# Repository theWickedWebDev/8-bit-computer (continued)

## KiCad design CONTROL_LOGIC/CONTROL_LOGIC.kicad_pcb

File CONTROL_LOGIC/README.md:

# Display Module

MORE DETAILS TO COME

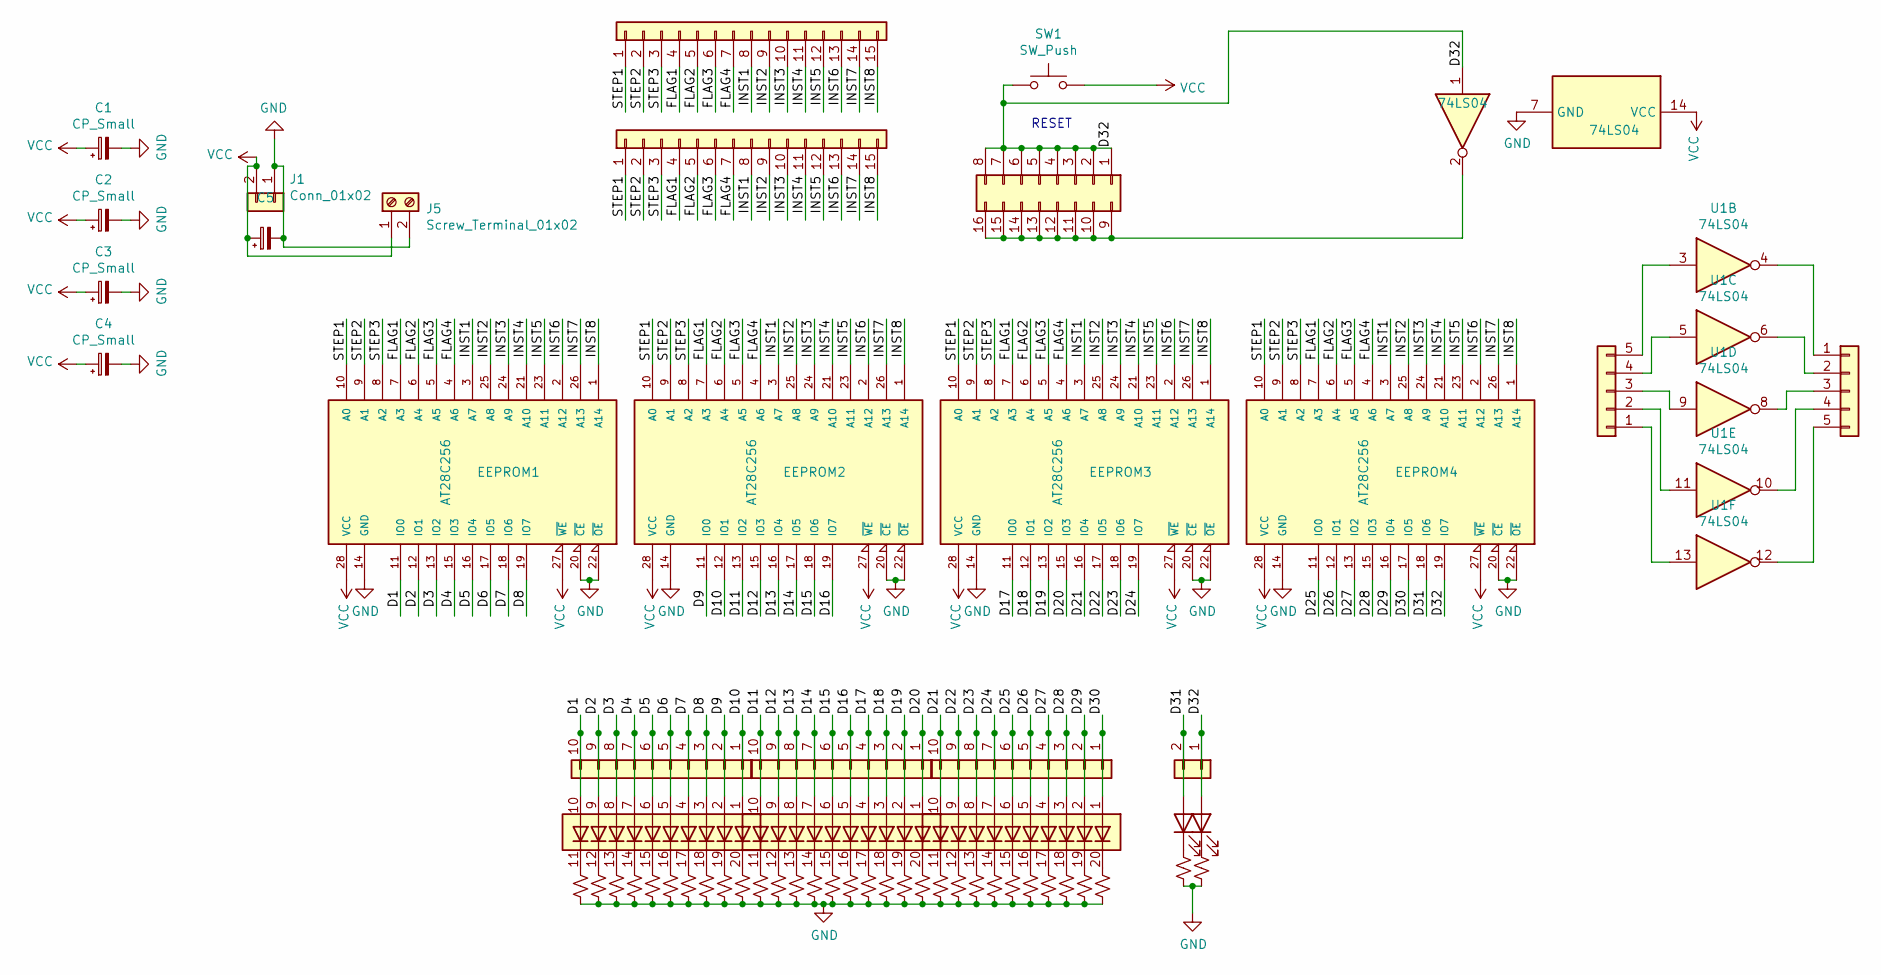
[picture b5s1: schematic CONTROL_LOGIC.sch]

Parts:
BAR1, BAR2, BAR3: HDSP-4850_2; HDSP-4850
C1, C2, C3, C4, C5: CP_Small; C_Radial_D5.0mm_H7.0mm_P2.00mm
D1, D2: LED; LED_D3.0mm
EEPROM1, EEPROM2, EEPROM3, EEPROM4: AT28C256; DIP-28_W15.24mm
J1, J9: Conn_01x02; PinHeader_1x02_P2.54mm_Vertical
J2, J6: Conn_01x15; PinHeader_1x15_P2.54mm_Vertical
J3, J7, J8: Conn_01x10; PinHeader_1x10_P2.54mm_Vertical
J4: Conn_2x08; PinHeader_2x08_P2.54mm_Vertical
J5: Screw_Terminal_01x02; TerminalBlock_bornier-2_P5.08mm
J10, J11: Conn_1x05; PinHeader_1x05_P2.54mm_Vertical
R1, R2, R3, R4, R5, R6, R7, R8, R9, R10, R11, R12, R13, R14, R15, R16, R17, R18, R19, R20, R21, R22, R23, R24, R25, R26, R27, R28, R29, R30, R31, R32: R_Small_US; R_Axial_DIN0204_L3.6mm_D1.6mm_P7.62mm_Horizontal
SW1: SW_Push; SW_PUSH_6mm
U1: 74LS04; DIP-14_W7.62mm

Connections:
/D1: BAR1.10 (A), EEPROM1.11 (IO0), J3.10
/D2: BAR1.9 (A), EEPROM1.12 (IO1), J3.9
/D3: BAR1.8 (A), EEPROM1.13 (IO2), J3.8
/D4: BAR1.7 (A), EEPROM1.15 (IO3), J3.7
/D5: BAR1.6 (A), EEPROM1.16 (IO4), J3.6
/D6: BAR1.5 (A), EEPROM1.17 (IO5), J3.5
/D7: BAR1.4 (A), EEPROM1.18 (IO6), J3.4
/D8: BAR1.3 (A), EEPROM1.19 (IO7), J3.3
/D9: BAR1.2 (A), EEPROM2.11 (IO0), J3.2
/D10: BAR1.1 (A), EEPROM2.12 (IO1), J3.1
/D11: BAR2.10 (A), EEPROM2.13 (IO2), J7.10
/D12: BAR2.9 (A), EEPROM2.15 (IO3), J7.9
/D13: BAR2.8 (A), EEPROM2.16 (IO4), J7.8
/D14: BAR2.7 (A), EEPROM2.17 (IO5), J7.7
/D15: BAR2.6 (A), EEPROM2.18 (IO6), J7.6
/D16: BAR2.5 (A), EEPROM2.19 (IO7), J7.5
/D17: BAR2.4 (A), EEPROM3.11 (IO0), J7.4
/D18: BAR2.3 (A), EEPROM3.12 (IO1), J7.3
/D19: BAR2.2 (A), EEPROM3.13 (IO2), J7.2
/D20: BAR2.1 (A), EEPROM3.15 (IO3), J7.1
/D21: BAR3.10 (A), EEPROM3.16 (IO4), J8.10
/D22: BAR3.9 (A), EEPROM3.17 (IO5), J8.9
/D23: BAR3.8 (A), EEPROM3.18 (IO6), J8.8
/D24: BAR3.7 (A), EEPROM3.19 (IO7), J8.7
/D25: BAR3.6 (A), EEPROM4.11 (IO0), J8.6
/D26: BAR3.5 (A), EEPROM4.12 (IO1), J8.5
/D27: BAR3.4 (A), EEPROM4.13 (IO2), J8.4
/D28: BAR3.3 (A), EEPROM4.15 (IO3), J8.3
/D29: BAR3.2 (A), EEPROM4.16 (IO4), J8.2
/D30: BAR3.1 (A), EEPROM4.17 (IO5), J8.1
/D31: D1.2 (A), EEPROM4.18 (IO6), J9.2
/D32: D2.2 (A), EEPROM4.19 (IO7), J4.1, J4.2, J4.3, J4.4, J4.5, J4.6, J4.7, J4.8, J9.1, SW1.1, U1.1
/FLAG1: EEPROM1.7 (A3), EEPROM2.7 (A3), EEPROM3.7 (A3), EEPROM4.7 (A3), J2.4, J6.4
/FLAG2: EEPROM1.6 (A4), EEPROM2.6 (A4), EEPROM3.6 (A4), EEPROM4.6 (A4), J2.5, J6.5
/FLAG3: EEPROM1.5 (A5), EEPROM2.5 (A5), EEPROM3.5 (A5), EEPROM4.5 (A5), J2.6, J6.6
/FLAG4: EEPROM1.4 (A6), EEPROM2.4 (A6), EEPROM3.4 (A6), EEPROM4.4 (A6), J2.7, J6.7
/INST1: EEPROM1.3 (A7), EEPROM2.3 (A7), EEPROM3.3 (A7), EEPROM4.3 (A7), J2.8, J6.8
/INST2: EEPROM1.25 (A8), EEPROM2.25 (A8), EEPROM3.25 (A8), EEPROM4.25 (A8), J2.9, J6.9
/INST3: EEPROM1.24 (A9), EEPROM2.24 (A9), EEPROM3.24 (A9), EEPROM4.24 (A9), J2.10, J6.10
/INST4: EEPROM1.21 (A10), EEPROM2.21 (A10), EEPROM3.21 (A10), EEPROM4.21 (A10), J2.11, J6.11
/INST5: EEPROM1.23 (A11), EEPROM2.23 (A11), EEPROM3.23 (A11), EEPROM4.23 (A11), J2.12, J6.12
/INST6: EEPROM1.2 (A12), EEPROM2.2 (A12), EEPROM3.2 (A12), EEPROM4.2 (A12), J2.13, J6.13
/INST7: EEPROM1.26 (A13), EEPROM2.26 (A13), EEPROM3.26 (A13), EEPROM4.26 (A13), J2.14, J6.14
/INST8: EEPROM1.1 (A14), EEPROM2.1 (A14), EEPROM3.1 (A14), EEPROM4.1 (A14), J2.15, J6.15
/STEP1: EEPROM1.10 (A0), EEPROM2.10 (A0), EEPROM3.10 (A0), EEPROM4.10 (A0), J2.1, J6.1
/STEP2: EEPROM1.9 (A1), EEPROM2.9 (A1), EEPROM3.9 (A1), EEPROM4.9 (A1), J2.2, J6.2
/STEP3: EEPROM1.8 (A2), EEPROM2.8 (A2), EEPROM3.8 (A2), EEPROM4.8 (A2), J2.3, J6.3
GND: C1.2, C2.2, C3.2, C4.2, C5.2, EEPROM1.14 (GND), EEPROM1.20 (~CE), EEPROM1.22 (~OE), EEPROM2.14 (GND), EEPROM2.20 (~CE), EEPROM2.22 (~OE), EEPROM3.14 (GND), EEPROM3.20 (~CE), EEPROM3.22 (~OE), EEPROM4.14 (GND), EEPROM4.20 (~CE), EEPROM4.22 (~OE), J1.1, J5.2, R1.2, R2.2, R3.2, R4.2, R5.2, R6.2, R7.2, R8.2, R9.2, R10.2, R11.2, R12.2, R13.2, R14.2, R15.2, R16.2, R17.2, R18.2, R19.2, R20.2, R21.2, R22.2, R23.2, R24.2, R25.2, R26.2, R27.2, R28.2, R29.2, R30.2, R31.2, R32.2, U1.7 (GND)
unnamed: BAR1.11 (K), R3.1
unnamed: BAR1.12 (K), R4.1
unnamed: BAR1.13 (K), R5.1
unnamed: BAR1.14 (K), R6.1
unnamed: BAR1.15 (K), R7.1
unnamed: BAR1.16 (K), R8.1
unnamed: BAR1.17 (K), R9.1
unnamed: BAR1.18 (K), R10.1
unnamed: BAR1.19 (K), R11.1
unnamed: BAR1.20 (K), R12.1
unnamed: BAR2.11 (K), R13.1
unnamed: BAR2.12 (K), R14.1
unnamed: BAR2.13 (K), R15.1
unnamed: BAR2.14 (K), R16.1
unnamed: BAR2.15 (K), R17.1
unnamed: BAR2.16 (K), R18.1
unnamed: BAR2.17 (K), R19.1
unnamed: BAR2.18 (K), R20.1
unnamed: BAR2.19 (K), R21.1
unnamed: BAR2.20 (K), R22.1
unnamed: BAR3.11 (K), R23.1
unnamed: BAR3.12 (K), R24.1
unnamed: BAR3.13 (K), R25.1
unnamed: BAR3.14 (K), R26.1
unnamed: BAR3.15 (K), R27.1
unnamed: BAR3.16 (K), R28.1
unnamed: BAR3.17 (K), R29.1
unnamed: BAR3.18 (K), R30.1
unnamed: BAR3.19 (K), R31.1
unnamed: BAR3.20 (K), R32.1
unnamed: D1.1 (K), R1.1
unnamed: D2.1 (K), R2.1
unnamed: J4.9, J4.10, J4.11, J4.12, J4.13, J4.14, J4.15, J4.16, U1.2
unnamed: J10.1, U1.13
unnamed: J10.2, U1.11
unnamed: J10.3, U1.9
unnamed: J10.4, U1.5
unnamed: J10.5, U1.3
unnamed: J11.1, U1.4
unnamed: J11.2, U1.6
unnamed: J11.3, U1.8
unnamed: J11.4, U1.10
unnamed: J11.5, U1.12
VCC: C1.1, C2.1, C3.1, C4.1, C5.1, EEPROM1.27 (~WE), EEPROM1.28 (VCC), EEPROM2.27 (~WE), EEPROM2.28 (VCC), EEPROM3.27 (~WE), EEPROM3.28 (VCC), EEPROM4.27 (~WE), EEPROM4.28 (VCC), J1.2, J5.1, SW1.2, U1.14 (VCC)

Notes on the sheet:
RESET

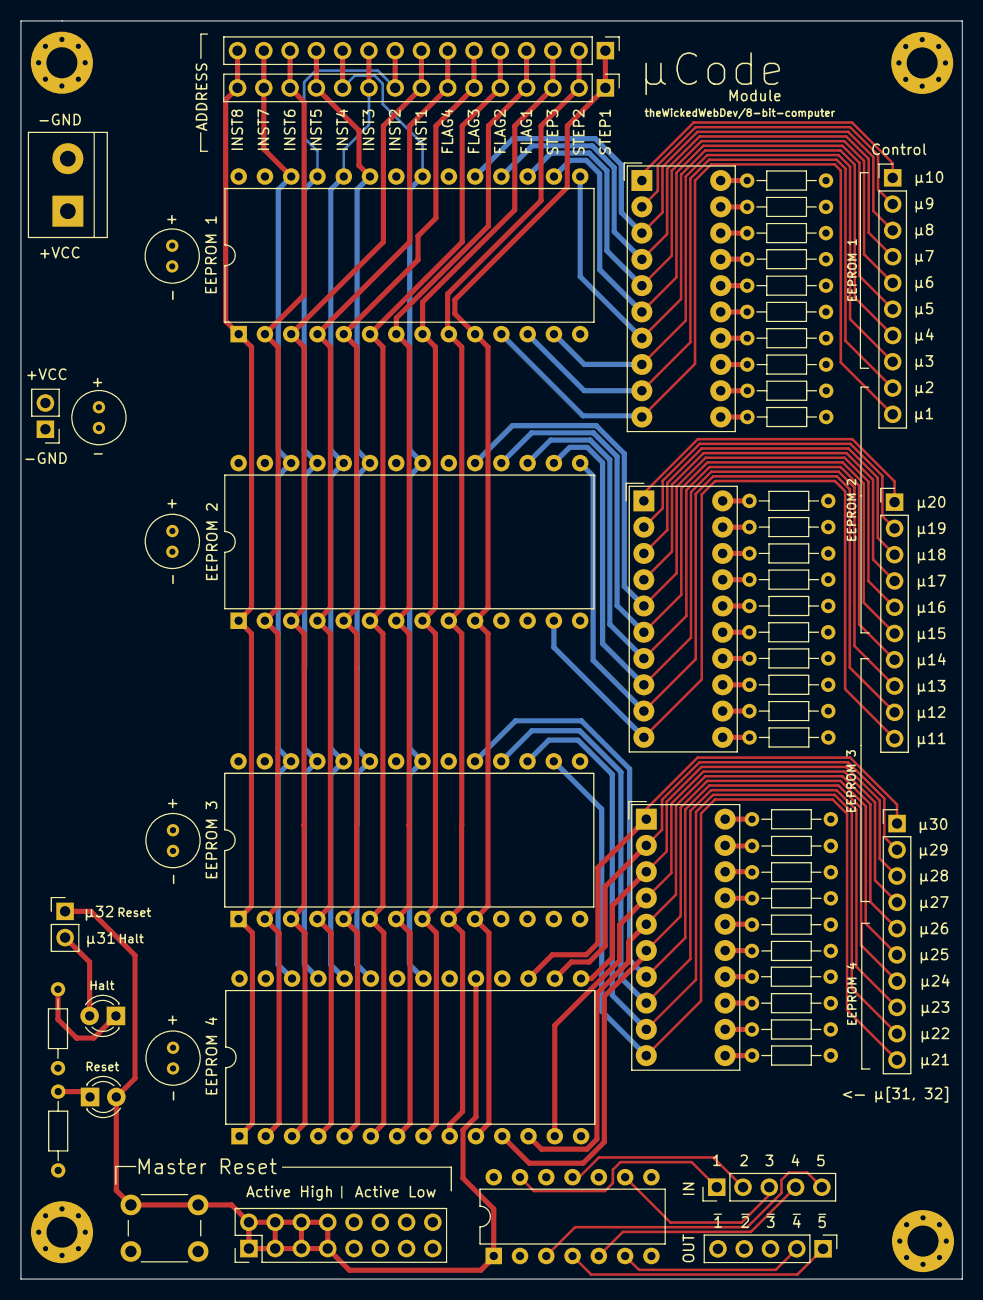
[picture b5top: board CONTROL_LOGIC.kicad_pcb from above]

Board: 4 copper layers, 91.0 x 121.6 mm, 59 parts (0 on the bottom side), 92 nets.

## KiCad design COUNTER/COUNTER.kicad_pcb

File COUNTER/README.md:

# 8 bit Counter

More details to come

## QA
✅ Tested this module and verified it works as expected

### Changes if I re-fabricate this again

- I should have added a `Carry In` pin so that I can chain multiple modules together to create 16, 24, 32bit, etc...

<br/>

## PCB

<br/>

Used to point to the programs next instruction in RAM. With each rising edge of the clock, it will increment by one. It is connected to the bus through a tri-state buffer that allows for output and input. Input is used to manually set the value on the counter which is used for conditional jumps.

<br/>

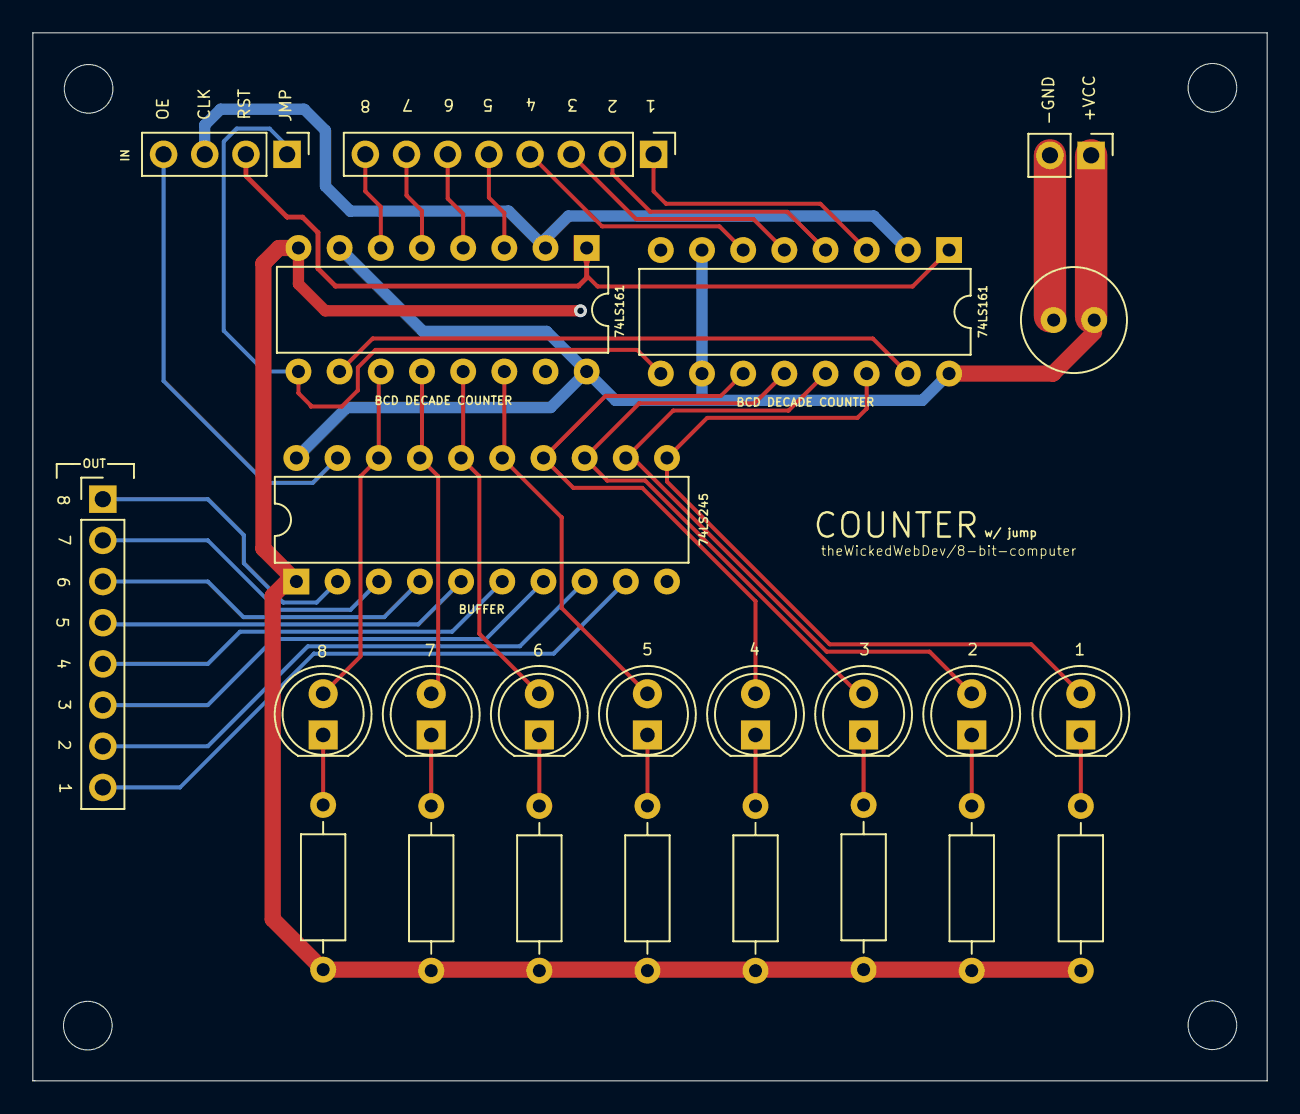
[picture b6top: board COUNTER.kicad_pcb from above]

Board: 2 copper layers, 76.1 x 64.6 mm, 24 parts (0 on the bottom side), 39 nets.

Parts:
C8: CP1; C_Radial_D6.3mm_H11.0mm_P2.50mm
D44, D45, D46, D47, D48, D49, D50, D51: LED; LED_D5.0mm
J1, J3: Conn_01x08; PinHeader_1x08_P2.54mm_Vertical
J2: Conn_01x04; PinHeader_1x04_P2.54mm_Vertical
J10: Conn_01x04; PinHeader_1x02_P2.54mm_Vertical
R11, R12, R13, R14, R15, R16, R17, R18: R_US; R_Axial_DIN0207_L6.3mm_D2.5mm_P10.16mm_Horizontal
U46, U48: 74LS161; DIP-16_W7.62mm
U47: 74LS245; DIP-20_W7.62mm

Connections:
/CLOCK: J2.3, U46.2, U48.2
/D1: J3.1, U48.3
/D2: J3.2, U48.4
/D3: J3.3, U48.5
/D4: J3.4, U48.6
/D5: J3.5, U46.3
/D6: J3.6, U46.4
/D7: J3.7, U46.5
/D8: J3.8, U46.6
/JUMP: J2.1, U46.9, U48.9
/OE: J2.4, U47.19
/RESET: J2.2, U46.1, U48.1
/Y1: J1.8, U47.9
/Y2: J1.7, U47.8
/Y3: J1.6, U47.7
/Y4: J1.5, U47.6
/Y5: J1.4, U47.5
/Y6: J1.3, U47.4
/Y7: J1.2, U47.3
/Y8: J1.1, U47.2
GND: C8.2, J10.2, R11.2, R12.2, R13.2, R14.2, R15.2, R16.2, R17.2, R18.2, U46.8, U47.1, U47.10, U48.8
unnamed: D44.1, R11.1
unnamed: D44.2, U46.11, U47.18
unnamed: D45.1, R12.1
unnamed: D45.2, U46.12, U47.17
unnamed: D46.1, R13.1
unnamed: D46.2, U46.13, U47.16
unnamed: D47.1, R14.1
unnamed: D47.2, U46.14, U47.15
unnamed: D48.1, R15.1
unnamed: D48.2, U47.14, U48.11
unnamed: D49.1, R16.1
unnamed: D49.2, U47.13, U48.12
unnamed: D50.1, R17.1
unnamed: D50.2, U47.12, U48.13
unnamed: D51.1, R18.1
unnamed: D51.2, U47.11, U48.14
unnamed: U46.10, U48.15
VCC: C8.1, J10.1, U46.7, U46.16, U47.20, U48.7, U48.10, U48.16

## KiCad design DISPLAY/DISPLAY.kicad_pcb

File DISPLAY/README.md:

# Display Module

MORE DETAILS TO COME

Uses a JK flip flop, a 555 timer and EEPROM to multiplex four 7-segment displays to output the current value of the bus in decimal.

<br/>

<br/><br/>

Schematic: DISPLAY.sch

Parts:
C16: CP1; C_Radial_D6.3mm_H11.0mm_P2.50mm
C133: CP; C_Disc_D6.0mm_W2.5mm_P5.00mm
C233: C; C_Disc_D6.0mm_W2.5mm_P5.00mm
J16: Conn_01x04; PinHeader_1x02_P2.54mm_Vertical
J1123: Conn_01x09; PinHeader_1x09_P2.54mm_Vertical
R1452, R2123: R_US; R_Axial_DIN0207_L6.3mm_D2.5mm_P10.16mm_Horizontal
U1, U2, U3, U102: HDSP-7503; 7SegmentLED_LTS6760_LTS6780
U9: AT28C256; DIP-28_W15.24mm
U1555: NE55P; DIP-8_W7.62mm
U2444: 74LS76; DIP-16_W7.62mm
U4332: 74LS139; DIP-16_W7.62mm

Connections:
/A: U1.7, U2.7, U3.7, U9.11 (IO0), U102.7
/B: U1.6, U2.6, U3.6, U9.12 (IO1), U102.6
/C: U1.4, U2.4, U3.4, U9.13 (IO2), U102.4
/CLOCK_DISPLAY: U1555.3 (Q), U2444.6 (C)
/D: U1.2, U2.2, U3.2, U9.15 (IO3), U102.2
/E: U1.1, U2.1, U3.1, U9.16 (IO4), U102.1
/F: U1.9, U2.9, U3.9, U9.17 (IO5), U102.9
/G: U1.10, U2.10, U3.10, U9.18 (IO6), U102.10
/H: U9.19 (IO7)
GND: C16.2, C133.1, C233.2, J16.2, U9.1 (A14), U9.2 (A12), U9.14 (GND), U9.20 (~CE), U9.22 (~OE), U9.23 (A11), U9.26 (A13), U1555.1 (GND), U2444.13 (GND), U4332.1 (E), U4332.8 (GND)
unnamed: C133.2, U1555.2 (TR)
unnamed: C233.1, U1555.5 (CV)
unnamed: J1123.1, U9.21 (A10)
unnamed: J1123.2, U9.3 (A7)
unnamed: J1123.3, U9.4 (A6)
unnamed: J1123.4, U9.5 (A5)
unnamed: J1123.5, U9.6 (A4)
unnamed: J1123.6, U9.7 (A3)
unnamed: J1123.7, U9.8 (A2)
unnamed: J1123.8, U9.9 (A1)
unnamed: J1123.9, U9.10 (A0)
unnamed: R1452.1, R2123.1, U1555.7 (DIS)
unnamed: R1452.2, U1555.6 (THR)
unnamed: U1.3, U1.8, U4332.7 (O3)
unnamed: U2.3, U2.8, U4332.6 (O2)
unnamed: U3.3, U3.8, U4332.5 (O1)
unnamed: U102.3, U102.8, U4332.4 (O0)
unnamed: U9.25 (A8), U2444.1 (C), U2444.10 (~Q), U4332.2 (A0)
unnamed: U9.24 (A9), U2444.15 (Q), U4332.3 (A1)
VCC: C16.1, J16.1, R2123.2, U9.27 (~WE), U9.28 (VCC), U1555.8 (VCC), U2444.2 (~S), U2444.3 (~R), U2444.4 (J), U2444.5 (VCC), U2444.7 (~S), U2444.8 (~R), U2444.9 (J), U2444.12 (K), U2444.16 (K), U4332.16 (VCC)

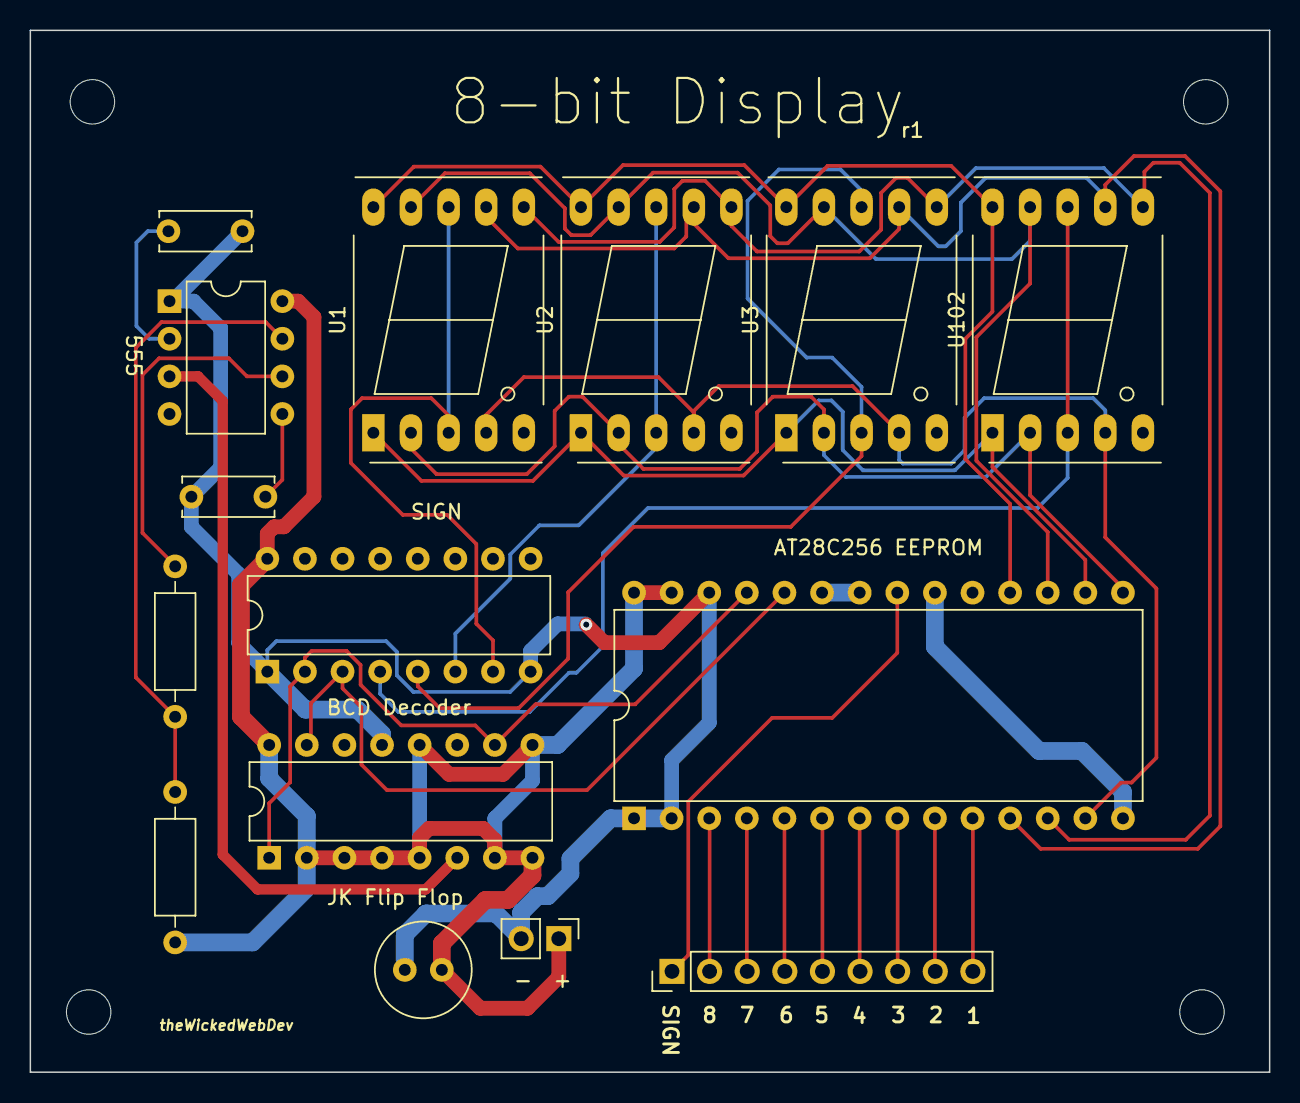
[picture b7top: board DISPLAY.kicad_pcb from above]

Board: 2 copper layers, 83.7 x 70.4 mm, 15 parts (0 on the bottom side), 29 nets.
